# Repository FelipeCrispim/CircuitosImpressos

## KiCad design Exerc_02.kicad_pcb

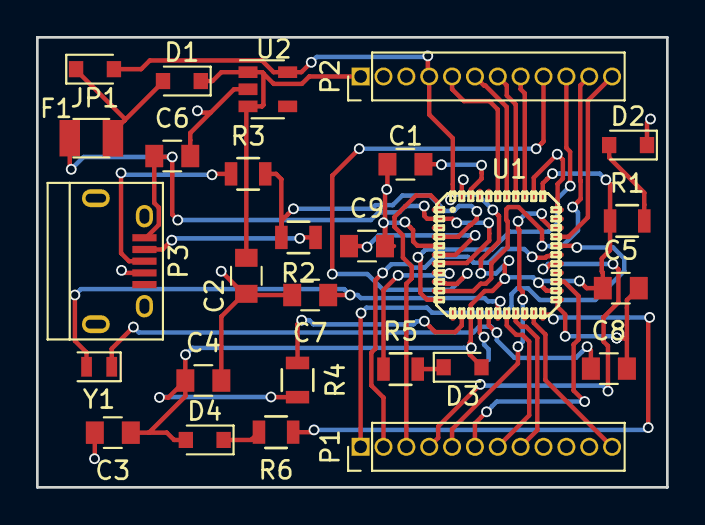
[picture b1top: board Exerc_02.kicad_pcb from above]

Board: 2 copper layers, 35.0 x 25.0 mm, 27 parts (0 on the bottom side), 35 nets.

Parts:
C1, C5: 0.1uF; C_0805
C2, C3: 10uF; C_0805
C4, C6, C9: 1uF; C_0805
C7, C8: 22pF; C_0805
D1: D; D_0805
D2: RED; D_0805
D3: GREEN; D_0805
D4: YELLOW; D_0805
F1: Fuse_Small; Fuse_SMD1206_Reflow
JP1: Jumper; D_0805
P1: JP7; Socket_Strip_Straight_1x12_Pitch1.27mm
P2: JP6; Socket_Strip_Straight_1x12_Pitch1.27mm
P3: USB_A; USB_Micro-B
R1: 1k; R_0805
R2, R3: 22; R_0805
R4: 10K; R_0805
R5, R6: 330; R_0805
U1: ATmega32U4; MLF-44_Atmel
U2: MIC5219; SOT-23-5
Y1: Crystal; Crystal_SMD_2012-2pin_2.0x1.2mm

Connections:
A0: P2.8, U1.36
A1: P2.7, U1.37
A2: P2.6, U1.38
A3: P2.5, U1.39
D2: P1.8, U1.19
D3: P1.7, U1.18
D4: P1.6, U1.25
D5: P1.5, U1.31
D6: P1.4, U1.27
D7: P1.3, U1.1
D8: P1.2, U1.28
D9: P1.1, U1.29
D10: P2.12, U1.30
D+: R2.2, R3.2, U1.4
GND: C1.2, C2.2, C3.2, C4.2, C5.2, C6.2, C7.2, C8.2, C9.2, D2.1, P1.9, P1.10, P2.2, P3.4, U1.5, U1.15, U1.23, U1.33, U1.35, U1.43, U2.2
MISO: P2.10, U1.11
MOSI: P2.11, U1.10
unnamed: C1.1, U1.42
unnamed: C7.1, U1.17, Y1.2
unnamed: C8.1, U1.16, Y1.1
unnamed: C9.1, U1.6
unnamed: D1.2, F1.2, JP1.1
unnamed: D2.2, R1.2
unnamed: D3.1, R5.2
unnamed: D4.1, R6.2
unnamed: P3.2, R2.1
unnamed: P3.3, R3.1
unnamed: R4.1, U1.13
unnamed: R5.1, U1.8
unnamed: R6.1, U1.22
RAW: C2.1, D1.1, P2.1, U2.1, U2.3
SCK: P2.9, U1.9
TX0: P1.12, U1.21
UVCC: C6.1, F1.1, P3.1, U1.2, U1.7
VCC: C3.1, C4.1, C5.1, D3.2, D4.2, JP1.2, P2.4, R1.1, R4.2, U1.14, U1.24, U1.34, U1.44, U2.5

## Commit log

2017-02-14 Adicionado arquivos
2017-02-16 Começado PCB
2017-02-16 Finalizado PCB
2017-02-17 Atualizado algumas trilhas.
